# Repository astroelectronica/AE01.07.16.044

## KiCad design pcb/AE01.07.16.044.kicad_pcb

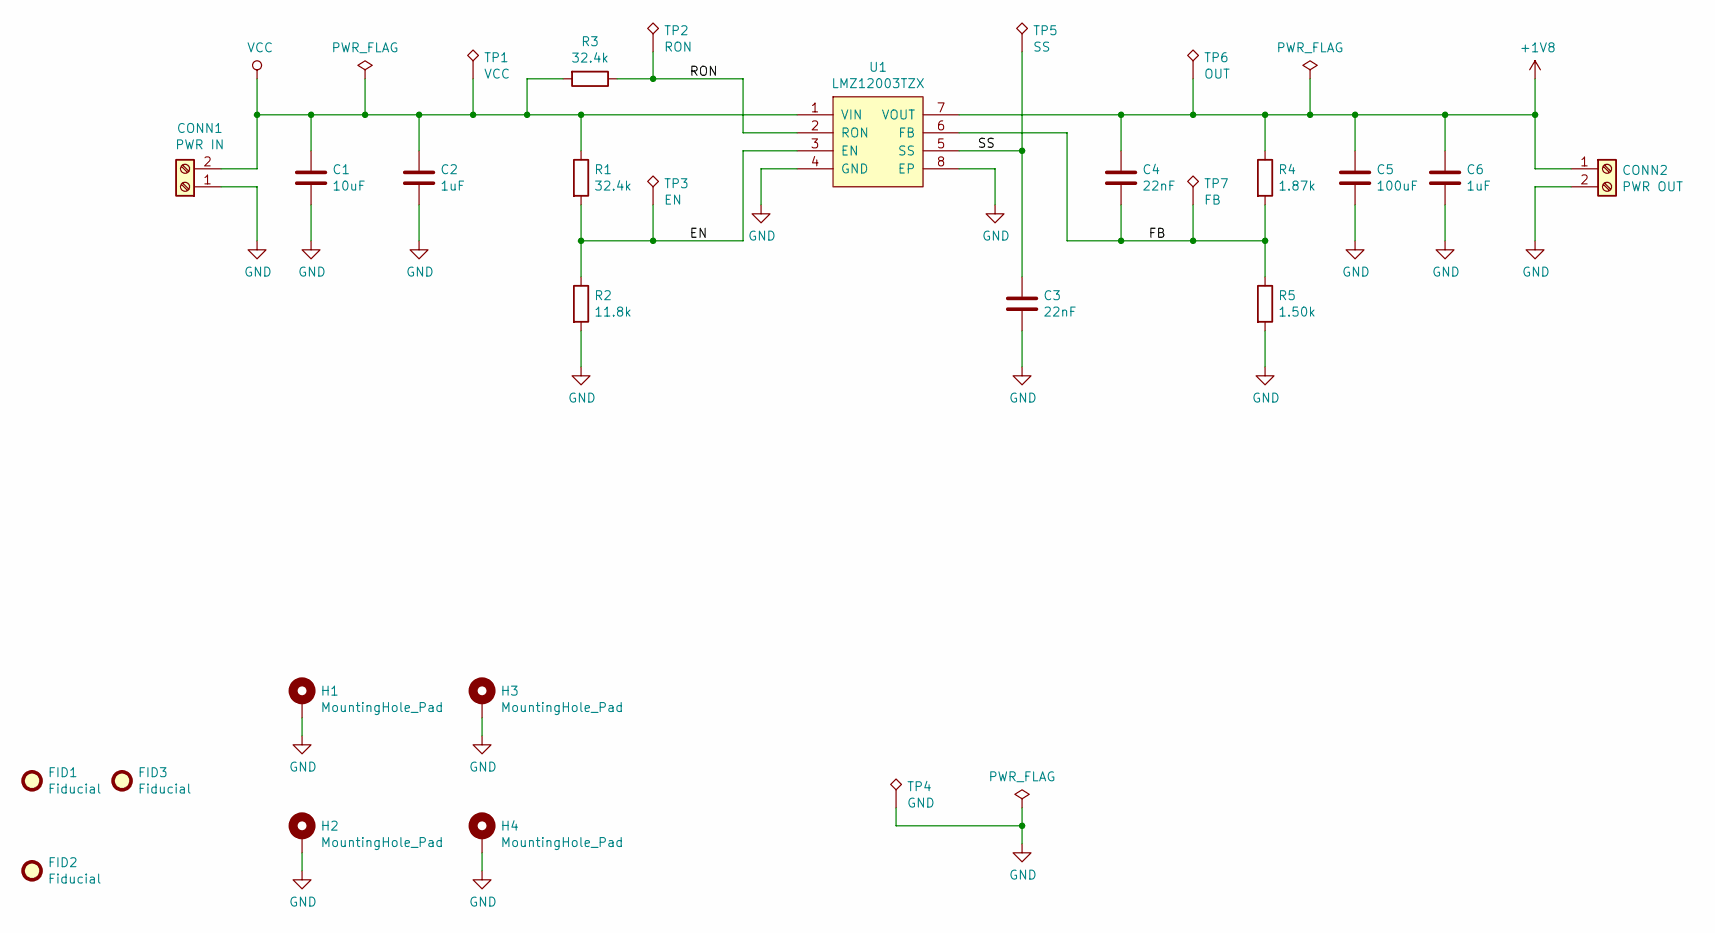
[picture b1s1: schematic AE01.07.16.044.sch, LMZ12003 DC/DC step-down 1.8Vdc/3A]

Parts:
C1: 10uF; C_1210_3225Metric; MPN C3225X5R1H106K250AB
C2, C6: 1uF; C_1206_3216Metric; MPN C3216X7R1H105K160AE
C3, C4: 22nF; C_0805_2012Metric; MPN C2012X7R2A223K125AE
C5: 100uF; C_1206_3216Metric; MPN C3216X5R0J107M160AB
CONN1: PWR IN; TerminalBlock_Phoenix_MPT-0,5-2-2.54_1x02_P2.54mm_Horizontal; MPN 1725656
CONN2: PWR OUT; TerminalBlock_Phoenix_MPT-0,5-2-2.54_1x02_P2.54mm_Horizontal; MPN 1725656
FID1, FID2, FID3: Fiducial; Fiducial_0.5mm_Mask1.5mm
H1, H2, H3, H4: MountingHole_Pad; MountingHole_3.2mm_M3_Pad_Via
R1, R3: 32.4k; R_0805_2012Metric; MPN RC0805FR-0732K4L
R2: 11.8k; R_0805_2012Metric; MPN RC0805FR-0711K8L
R4: 1.87k; R_0805_2012Metric; MPN RC0805FR-071K87L
R5: 1.50k; R_0805_2012Metric; MPN RC0805FR-071K5L
TP1: VCC; TestPoint_Pad_D2.0mm
TP2: RON; TestPoint_Pad_D2.0mm
TP3: EN; TestPoint_Pad_D2.0mm
TP4: GND; TestPoint_Keystone_5010-5014_Multipurpose; MPN 5011
TP5: SS; TestPoint_Pad_D2.0mm
TP6: OUT; TestPoint_Pad_D2.0mm
TP7: FB; TestPoint_Pad_D2.0mm
U1: LMZ12003TZX; TO-263-7_TabPin8; MPN LMZ12003TZX-ADJ/NOPB

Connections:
+1V8: C4.1, C5.1, C6.1, CONN2.1, R4.1, TP6.1, U1.7 (VOUT)
/EN: R1.2, R2.1, TP3.1, U1.3 (EN)
/FB: C4.2, R4.2, R5.1, TP7.1, U1.6 (FB)
/RON: R3.1, TP2.1, U1.2 (RON)
/SS: C3.1, TP5.1, U1.5 (SS)
GND: C1.2, C2.2, C3.2, C5.2, C6.2, CONN1.1, CONN2.2, H1.1, H2.1, H3.1, H4.1, R2.2, R5.2, TP4.1, U1.4 (GND), U1.8 (EP)
VCC: C1.1, C2.1, CONN1.2, R1.1, R3.2, TP1.1, U1.1 (VIN)

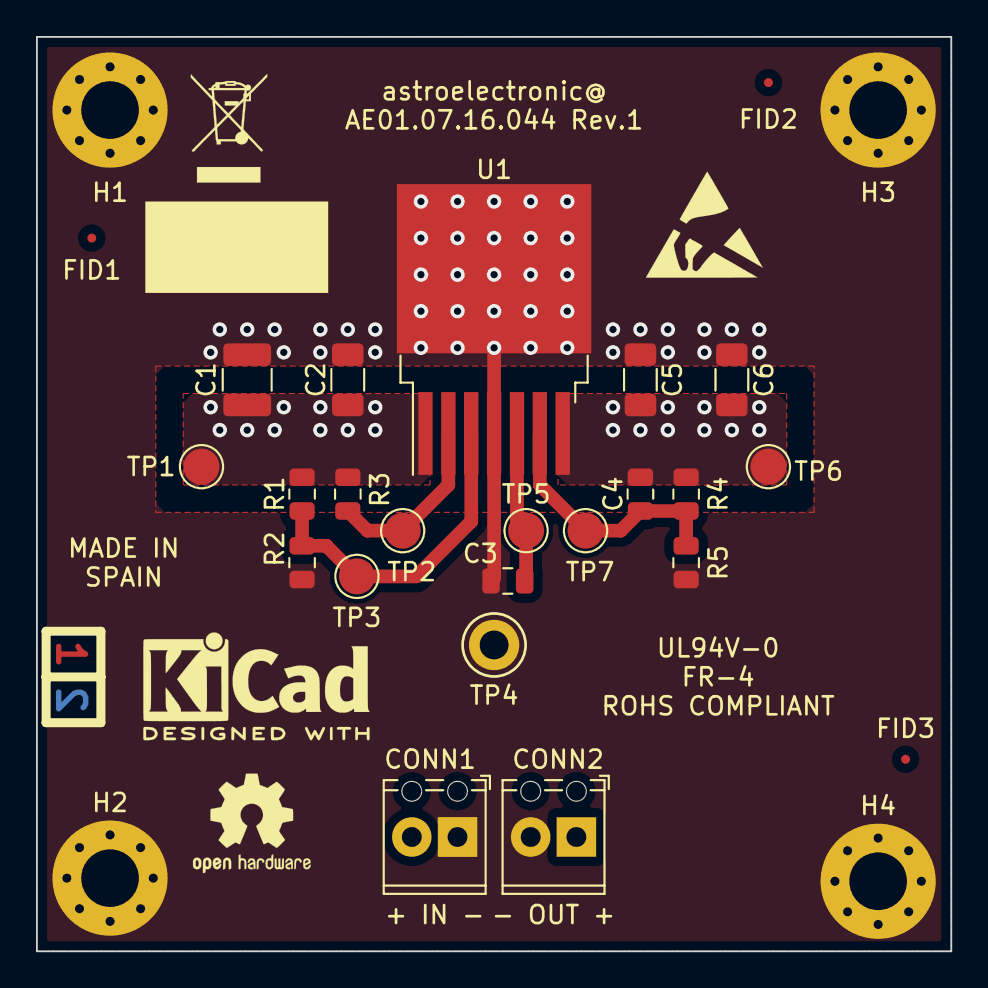
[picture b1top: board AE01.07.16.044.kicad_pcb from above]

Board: 2 copper layers, 50.8 x 50.8 mm, 28 parts (0 on the bottom side), 7 nets.
